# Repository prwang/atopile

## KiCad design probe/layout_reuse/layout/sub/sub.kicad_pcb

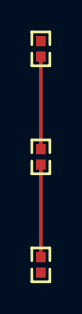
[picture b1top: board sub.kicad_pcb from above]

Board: 2 copper layers, 3 parts (0 on the bottom side), 2 nets.

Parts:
R1, R2, R3: 1kΩ ±1%; R0402

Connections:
unnamed[0]-1: R1.2, R2.1
unnamed[0]-2: R2.2, R3.1

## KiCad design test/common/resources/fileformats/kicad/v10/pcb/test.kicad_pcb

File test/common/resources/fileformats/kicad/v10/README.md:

# KiCad v10 dialect corpus (`(version 20260206)`)

Paired with the same-stem files in `../v9/pcb/` for cross-dialect equivalence
tests. Generated 2026-06-12 with kicad-cli 10.0.3:

| file | origin | v9 pair |
|---|---|---|
| `pcb/test.kicad_pcb` | `kicad-cli pcb upgrade --force` of `v9/pcb/test.kicad_pcb` | yes |
| `pcb/layout_reuse_top.kicad_pcb` | upgrade of an atopile-built `examples/layout_reuse` top board (contains atopile groups, placement rule area, manual segments) | yes |
| `pcb/interf_u_unrouted.kicad_pcb` | upgrade of KiCadRoutingTools `kicad_files/interf_u_unrouted.kicad_pcb` (real-world KiCad-authored board, many nets) | yes |
| `pcb/lvds_converter_dualclk.kicad_pcb` | copied verbatim from KiCadRoutingTools — **natively saved by KiCad 10**, not an upgrade artifact | no (no v9 original exists) |
| `pcb/padstacks_complex.kicad_pcb` | `kicad-cli pcb upgrade --force` of the KiCad QA board `qa/data/pcbnew/padstacks_complex.kicad_pcb` — pad-level `(padstack (mode front_inner_back\|custom) ...)` with per-layer shape/size/roundrect/chamfer overrides | no |
| `pcb/teardrop_elongated_pad.kicad_pcb` | upgrade of the KiCad QA board `teardrop_elongated_pad` — pad-level `(teardrops ...)`, board-level `(property ...)` text variables | no |
| `pcb/two_segment_teardrop.kicad_pcb` | upgrade of the KiCad QA board `two_segment_teardrop` — via-level `(teardrops ...)`, teardrop zones `(attr (teardrop (type padvia)))`, via + setup IPC-4761 treatments | no |
| `pcb/via_treatments.kicad_pcb` | KiCad QA board `padstacks` + hand-added vias (buried/micro, backdrill, tertiary_drill, front/back_post_machining, start_end_only, via padstack front_inner_back + custom, via teardrops), then normalized by `kicad-cli pcb upgrade --force` 10.0.3 so every byte is KiCad-authored; also exhibits blind vias, tri-state `(tenting (front none) ...)`, empty `(zone_layer_connections)`, flat pad chamfer, custom-pad primitives (gr_line/rect/bbox/arc/circle/poly). **Resave-stable** (2026-07-03): the fixture is the byte fixpoint of `kicad-cli pcb upgrade --force` over our own rewrite — the two hand-added orphan vias carry the netcode KiCad's connectivity rebuild assigns (`B`), so a resave is a strict no-op, not just semantics-preserving | no |
| `pcb/zone_arc_tuning.kicad_pcb` | hand-authored minimal board for arc-bearing `(pts ...)` chains + D5 room binding: a filled GND zone with a MID-chain outline arc, a separate keepout rule area with `(placement (enabled yes) (component_class "CLASSA"))`, a footprint with `(component_classes ...)`, and a `(generated (type tuning_pattern) ...)` whose base_line carries a mid-chain arc; normalized to the `kicad-cli pcb upgrade --force` 10.0.3 byte fixpoint (2026-07-03: previously one filled net-carrying zone held both `(net "GND")` and the placement — a state KiCad 10.0.3 never writes, which a resave converted to a net-less rule area; the two concerns are now separate zones and a resave is a strict no-op) | no |
| `pcb/tuning_generators_load_save.kicad_pcb` | `kicad-cli pcb upgrade --force` of the KiCad QA board `qa/data/pcbnew/tuning_generators_load_save.kicad_pcb` — a real GUI-authored `(generated (type tuning_pattern) ...)` single-mode serpentine with the full alphabetical property map (base_line pts, origin/end xy, target_length/_delay/_skew triples, ...) and 47 sorted quoted member uuids | no |
| `pcb/tuning_diffpair_synth.kicad_pcb` | synthesized from `tuning_generators_load_save` (no upstream diff-pair QA sample exists): tuning_mode `diff_pair` + `base_line_coupled` pts, validated by a round-trip through the real KiCad parser+formatter (`kicad-cli pcb upgrade --force` 10.0.3 preserved it verbatim) | no |

Key v10 dialect properties these files exhibit (vs v9):

- **No top-level net table at all.** Nets exist only as `(net "<name>")`
  references at point of use (pads, segments, vias, zones). Numbers are gone
  from the file entirely; zones lost the redundant `(net_name ...)` field;
  net-less zones (keepouts) simply omit the net clause.
- Pad-surface handling fields are nested: `(tenting front back)` →
  `(tenting (front yes) (back yes))` — applies to via/pad padstacks.
- Assorted new/changed keys (plot params, `duplicate_pad_numbers_are_jumpers`,
  `locked` removal, layer id renumbering, ...). The authoritative inventory is
  whatever the data-loss tests in `test/libs/kicad/test_fileformats_corpus.py`
  report — not this README.

Excluded for repo size (regenerate locally if needed):
KiCadRoutingTools boards `flat_hierarchy` (807K), `kit-dev-coldfire-xilinx_5213`
(2.3M), `sonde_u`, `haasoscope_pro_max_test`, and `lvds_converter_dualclk_gnd`
(native v10, near-duplicate of the included lvds board). Command:
`kicad-cli pcb upgrade --force <copy-of-board>.kicad_pcb`
(note: upgrade also emits a stray `.kicad_prl` next to the file — discard it).

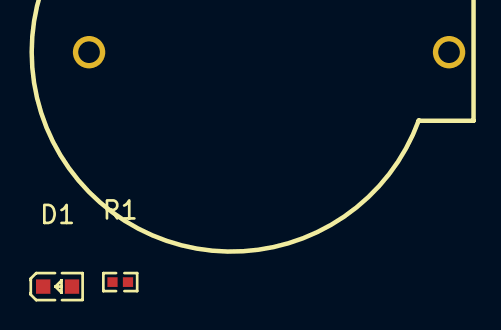
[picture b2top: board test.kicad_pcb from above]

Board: 2 copper layers, 3 parts (0 on the bottom side), 3 nets, no tracks yet.

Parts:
B1: ButtonCell; BAT-TH_BS-02-A1AJ010
D1: LED; LED0603-RD-YELLOW
R1: 40.2Ω; R0402

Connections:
B1-1-R1-2: B1.1, R1.2
B1-2-D1-2: B1.2, D1.2
D1-1-R1-1: D1.1, R1.1

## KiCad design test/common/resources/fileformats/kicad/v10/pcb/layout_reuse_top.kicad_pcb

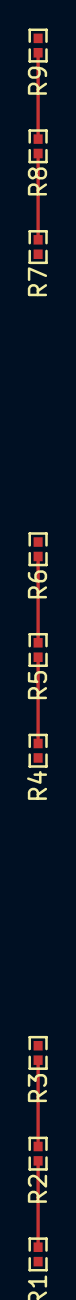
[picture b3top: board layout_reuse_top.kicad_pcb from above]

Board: 2 copper layers, 9 parts (0 on the bottom side), 9 nets.

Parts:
R1, R2, R3, R4, R5, R6, R7, R8, R9: 1kΩ ±1%; R0402

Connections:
sub_chains[0]-unnamed[0]: R1.2, R2.1
sub_chains[0]-unnamed[0]-1: R2.2, R3.1
sub_chains[1]-unnamed[0]: R4.2, R5.1
sub_chains[1]-unnamed[0]-1: R5.2, R6.1
sub_chains[2]-unnamed[0]: R7.2, R8.1
sub_chains[2]-unnamed[0]-1: R8.2, R9.1
unnamed[0]: R1.1, R9.2
unnamed[0]-1: R3.2, R4.1
unnamed[0]-2: R6.2, R7.1
